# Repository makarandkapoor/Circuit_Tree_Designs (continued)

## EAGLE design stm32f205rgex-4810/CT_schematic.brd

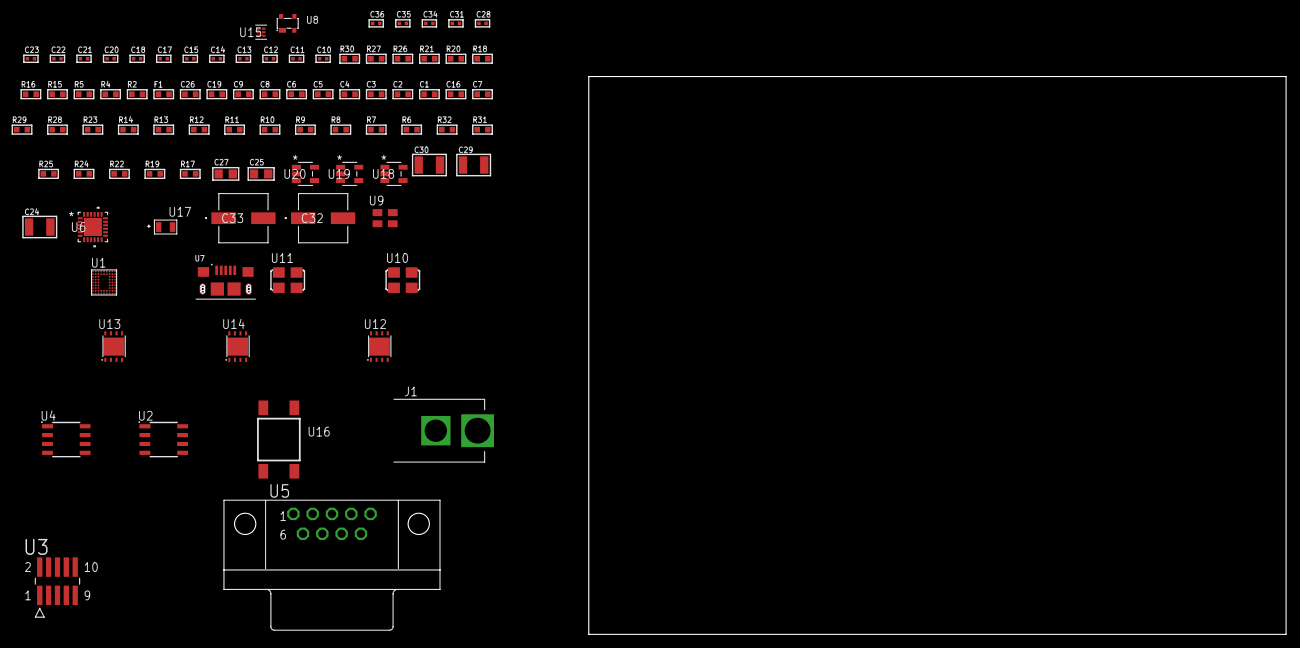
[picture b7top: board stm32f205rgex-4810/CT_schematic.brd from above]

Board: 2 copper layers, 88 parts (0 on the bottom side), 62 nets, no tracks yet.

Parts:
C1, C9, C19: 1e-06; C0603
C2, C3, C4, C5, C6: 1e-07; C0603
C7: 4.7e-06; C0603
C8: 1e-08; C0603
C10, C11, C13, C14, C31: 1e-07; C0402
C12, C15, C17, C18, C20, C21, C22, C23, C28, C34, C35, C36: 1e-08; C0402
C16: 2.2e-06; C0603
C24, C29, C30: 1e-05; C1210
C25, C27: 1e-05; C0805
C26: 8e-07; R0603
C32, C33: 0.0001; EXV-9H
F1: 240.0; L0603
J1: PJ-037B; PJ-037B_PACKAGE
R2, R21, R27: 1000.0; R0603
R4, R5: 4700.0; R0603
R6, R7, R8, R9, R10, R11, R12, R13, R14, R28, R29: 10000.0; R0603
R15: 5.0; R0603
R16: 120.0; R0603
R17: 470000.0; R0603
R18: 8060.0; R0603
R19, R22, R24, R25: 100000.0; R0603
R20: 200.0; R0603
R23: 36000.0; R0603
R26: 2231.0; R0603
R30: 9100.0; R0603
R31: 680000.0; R0603
R32: 120000.0; R0603
U1: STM32F205RGE6; EWLCSP66
U2: AT25010B-SSHL-T; SOIC-8
U3: FTSH-105-01-L-DV-K; SAMTEC_FTSH-105-01-L-DV-K
U4: SN65HVD230D; SOIC-8
U5: 182-009-113R531; 182-009-MALE
U6: USB3317C-CP-TR; QFN-24
U7: 10118193-0001LF; FCI_10118193-0001LF
U8: prtr5v0u2ax; SOT143B
U9: ASEK-32.768KHz-ECST; ASEK
U10: ASFL1-25MHZ-NCS; ASFL1
U11: ASFL1-26MHZ-NCS; ASFL1
U12, U14: LP3878SDX-ADJ/NOPB; WSON-8
U13: LP2951ACSDX/NOPB; WSON-8
U15: TPS3895ADRYR; SON-6
U16: 4-1437565-2; SW_4-1437565-2
U17: Q65110A2395; LGM67K-G1J2-24-Z
U18, U19, U20: nc7sz125m5x; NC7SZ125M5X

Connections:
CLK_U1_B9: U1.B9, U9.3
CLK_U1_E9: U1.E9, U10.3
CLK_U6_23: U6.23, U11.3
GND: C1.2, C2.2, C3.2, C4.2, C5.2, C6.2, C7.2, C8.2, C9.2, C10.2, C11.2, C12.2, C13.2, C14.2, C15.2, C16.2, C17.2, C18.2, C19.2, C20.2, C21.2, C22.2, C23.2, C24.2, C25.2, C26.2, C27.2, C28.2, C29.2, C30.2, C31.2, C32.2, C33.2, C34.2, C35.2, C36.2, J1.2, R2.2, R6.2, R7.2, R15.2, R17.2, R18.2, R21.2, R24.2, R27.2, R30.2, R32.2, U1.B1, U1.D8, U1.F1, U1.H9, U2.4, U3.3, U3.5, U4.2, U5.5, U6.25, U7.5, U7.6, U7.7, U7.8, U7.9, U8.1, U9.2, U10.2, U11.2, U12.3, U12.PAD, U13.3, U13.4, U13.PAD, U14.3, U14.PAD, U15.2, U17.C, U18.2, U18.3, U19.1, U19.3, U20.1, U20.3
NET_U1_B6: R6.1, U1.B6
NET_U1_C2: C11.1, U1.C2
NET_U1_C8: R8.1, U1.C8
NET_U1_E8: R4.1, U1.E8, U19.4
NET_U1_F7: C8.1, C9.1, F1.1, U1.F7
NET_U1_H7: R7.1, U1.H7
NET_U1_J9: U16.3, U16.4
NET_U2_3: R9.1, U2.3
NET_U2_7: R11.1, U2.7
NET_U3_9: R15.1, U3.9
NET_U4_6: R16.2, U4.6
NET_U4_8: R17.1, U4.8
NET_U5_2: R16.2, U4.6, U5.2
NET_U5_3: R16.1, U4.7, U5.3
NET_U6_4: C16.1, U6.4
NET_U6_22: R5.1, U6.22, U20.4
NET_U6_24: R18.1, U6.24
NET_U7_1: C19.1, U6.2, U7.1, U8.4
NET_U7_2: U6.5, U7.2, U8.3
NET_U7_3: U6.6, U7.3, U8.2
NET_U12_1: C23.1, U12.1
NET_U12_6: R20.2, R21.1, U12.6
NET_U12_8: R19.1, U12.8
NET_U13_5: R22.1, U13.5
NET_U13_7: R23.2, R24.1, U13.7
NET_U14_1: C28.1, U14.1
NET_U14_6: R26.2, R27.1, U14.6
NET_U14_8: R25.1, U14.8
NET_U15_1: R29.1, R30.1, U15.1
NET_U15_3: R31.2, R32.1, U15.3
NET_U15_4: R28.1, U15.4, U18.4, U19.2, U20.2
NET_U16_1: R2.1, U16.1, U16.2
PROC_CAN1_RX: U1.B7, U4.4
PROC_CAN1_TX: U1.A7, U4.1
PROC_SPI3_MISO: U1.B4, U2.2
PROC_SPI3_MOSI: U1.A3, U2.5
PROC_SPI3_NSS: R10.1, U1.A2, U2.1
PROC_SPI3_SCK: U1.B3, U2.6
PROC_SYS_JTCK_SWCLK: R13.1, U1.A1, U3.4
PROC_SYS_JTDO_SWO: U1.A4, U3.6
PROC_SYS_JTMS_SWDIO: R14.1, U1.B2, U3.2
PROC_USB_OTG_HS_ULPI_CK: U1.H6, U6.12
PROC_USB_OTG_HS_ULPI_D0: U1.G7, U6.16
PROC_USB_OTG_HS_ULPI_D1: U1.J6, U6.15
PROC_USB_OTG_HS_ULPI_D2: U1.J5, U6.14
PROC_USB_OTG_HS_ULPI_D3: U1.H3, U6.13
PROC_USB_OTG_HS_ULPI_D4: U1.J2, U6.11
PROC_USB_OTG_HS_ULPI_D5: U1.J1, U6.10
PROC_USB_OTG_HS_ULPI_D6: U1.H2, U6.9
PROC_USB_OTG_HS_ULPI_D7: U1.A5, U6.8
PROC_USB_OTG_HS_ULPI_DIR: U1.D7, U6.19
PROC_USB_OTG_HS_ULPI_NXT: U1.G8, U6.18
PROC_USB_OTG_HS_ULPI_STP: U1.G9, U6.20
RST_OUT_U3_JTAG_RST_B: R12.1, U3.10, U18.1
VCC_S1_12V2: C24.1, C26.1, C29.1, C32.1, C33.1, J1.1, R19.2, R25.2, U12.4, U13.8, U14.4
VCC_TIER1_1V2: C10.1, C25.1, R20.1, U1.J3, U12.5
VCC_TIER1_1V8: C18.1, C27.1, C34.1, C35.1, C36.1, R22.2, R23.1, U6.21, U13.1, U18.5, U19.5, U20.5
VCC_TIER1_3V3: C1.1, C2.1, C3.1, C4.1, C5.1, C6.1, C7.1, C12.1, C13.1, C14.1, C15.1, C17.1, C20.1, C21.1, C22.1, C30.1, C31.1, F1.2, R4.2, R5.2, R8.2, R9.2, R10.2, R11.2, R12.2, R13.2, R14.2, R26.1, R28.2, R29.2, R31.1, U1.A8, U1.A9, U1.D9, U1.E1, U2.8, U3.1, U4.3, U6.3, U6.17, U9.4, U10.4, U11.4, U14.5, U15.6

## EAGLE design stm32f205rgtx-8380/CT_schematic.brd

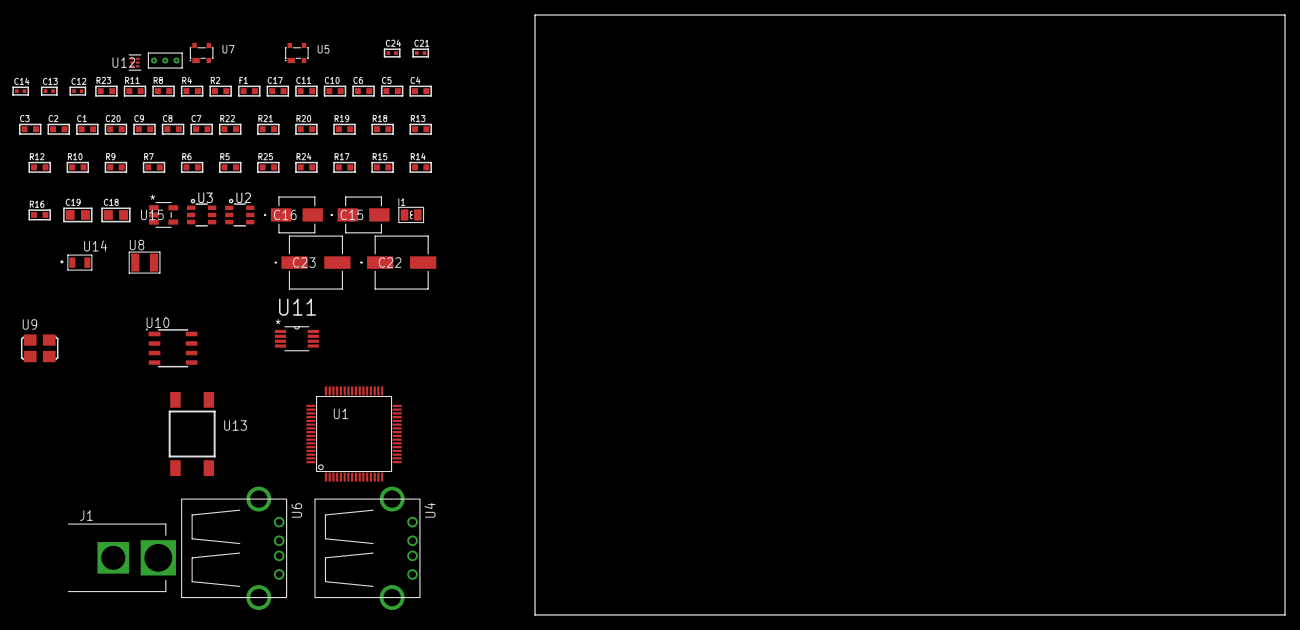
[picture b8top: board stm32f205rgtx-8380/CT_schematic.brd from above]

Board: 2 copper layers, 100.0 x 80.0 mm, 66 parts (0 on the bottom side), 39 nets, no tracks yet.

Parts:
C1, C11, C17: 1e-06; C0603
C2, C3, C4, C5, C6: 1e-07; C0603
C7: 4.7e-06; C0603
C8, C9: 2.2e-06; C0603
C10: 1e-08; C0603
C12, C13: 1e-11; C0402
C14, C24: 1e-08; C0402
C15: 1e-06; EXV-9B
C16: 2.2e-06; EXV-9B
C18, C19: 1e-05; C0805
C20: 1.6e-09; C0603
C21: 1e-07; C0402
C22, C23: 0.0001; EXV-9H
F1: 240.0; L0603
I1: 3.3e-06; L0806
J1: PJ-037B; PJ-037B_PACKAGE
R2: 1000.0; R0603
R4: 4700.0; R0603
R5, R6, R18: 47000.0; R0603
R7, R9, R10, R12, R13, R21, R22: 10000.0; R0603
R8, R11: 1270.0; R0603
R14, R15, R17: 100000.0; R0603
R16: 164658.62; R0603
R19: 56000.0; R0603
R20: 18000.0; R0603
R23: 9100.0; R0603
R24: 680000.0; R0603
R25: 120000.0; R0603
U1: STM32F205RGT6; LQFP64
U2, U3: MAX4995AAUT+T; SOT-23-6
U4, U6: 61400416021; USB-A-H
U5, U7: prtr5v0u2ax; SOT143B
U8: ABS07-32.768KHZ-7-T
U9: ASFL1-25MHZ-NCS; ASFL1
U10: LP2954AIMX/NOPB; LP2954
U11: TPS61085DGKR; MSOP-8
U12: TPS3895ADRYR; SON-6
U13: 4-1437565-2; SW_4-1437565-2
U14: Q65110A2395; LGM67K-G1J2-24-Z
U15: nc7sz125m5x; NC7SZ125M5X
U16: Dummy; DUMMY_PACKAGE_133

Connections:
CLK_CRYSTAL_U1_3: C12.1, U1.3, U8.1
CLK_CRYSTAL_U1_4: C13.1, U1.4, U8.2
CLK_U1_5: U1.5, U9.3
GND: C1.2, C2.2, C3.2, C4.2, C5.2, C6.2, C7.2, C8.2, C9.2, C10.2, C11.2, C12.2, C13.2, C14.2, C15.2, C16.2, C17.2, C18.2, C19.1, C19.2, C20.1, C20.2, C21.2, C22.2, C23.2, C24.2, J1.2, R2.2, R5.2, R6.2, R7.2, R8.2, R10.2, R11.2, R13.2, R17.2, R20.2, R23.2, R25.2, U1.12, U1.18, U1.63, U2.2, U3.2, U4.4, U4.5, U4.6, U5.1, U6.4, U6.5, U6.6, U7.1, U9.2, U10.4, U11.4, U12.2, U14.C, U15.1, U15.3, U16.1
NET_U1_7: R4.1, U1.7, U15.4
NET_U1_13: C10.1, C11.1, F1.1, U1.13
NET_U1_31: C8.1, U1.31
NET_U1_33: R11.1, U1.33
NET_U1_43: R8.1, U1.43
NET_U1_47: C9.1, U1.47
NET_U1_60: R7.1, U1.60
NET_U1_62: U13.3, U13.4
NET_U2_3: R5.1, U2.3
NET_U3_3: R6.1, U3.3
NET_U10_3: R15.1, U10.3
NET_U10_5: R14.1, U10.5
NET_U10_7: R16.2, R17.1, U10.7
NET_U11_1: R18.1, U11.1
NET_U11_2: R19.1, R20.1, U11.2
NET_U11_5: I1.1, U11.5
NET_U12_1: R22.1, R23.1, U12.1
NET_U12_3: R24.2, R25.1, U12.3
NET_U12_4: R21.1, U12.4, U15.2
NET_U13_1: R2.1, U13.1, U13.2
PROC_ADC1_IN1: U1.15, U16.3
PROC_ADC1_IN2: U1.16, U16.2
PROC_GPIO_TO_U1_USB_FAULT: R9.1, U1.6, U2.6
PROC_GPIO_TO_U1_USB_FAULT2: R12.1, U1.9, U3.6
PROC_GPIO_TO_U1_VBUS_EN: R10.1, U1.2, U2.4
PROC_GPIO_TO_U1_VBUS_EN2: R13.1, U1.8, U3.4
PROC_USB_OTG_FS_DM: U1.44, U4.2, U5.3
PROC_USB_OTG_FS_DP: U1.45, U4.3, U5.2
PROC_USB_OTG_FS_VBUS: U1.42, U2.1, U4.1, U5.4
PROC_USB_OTG_HS_DM: U1.35, U6.2, U7.3
PROC_USB_OTG_HS_DP: U1.36, U6.3, U7.2
PROC_USB_OTG_HS_VBUS: U1.34, U3.1, U6.1, U7.4
VCC_S1_4V7: C15.1, C17.1, C18.1, C22.1, C23.1, I1.2, J1.1, R15.2, U10.8, U11.3, U11.6
VCC_TIER1_3V3: C1.1, C2.1, C3.1, C4.1, C5.1, C6.1, C7.1, C14.1, C16.1, C21.1, C24.1, F1.2, R4.2, R9.2, R12.2, R14.2, R16.1, R21.2, R22.2, R24.1, U1.1, U1.19, U1.32, U1.48, U1.64, U9.4, U10.1, U12.6, U15.5
VCC_TIER1_5V0: C19.2, R19.2, U2.5, U3.5
